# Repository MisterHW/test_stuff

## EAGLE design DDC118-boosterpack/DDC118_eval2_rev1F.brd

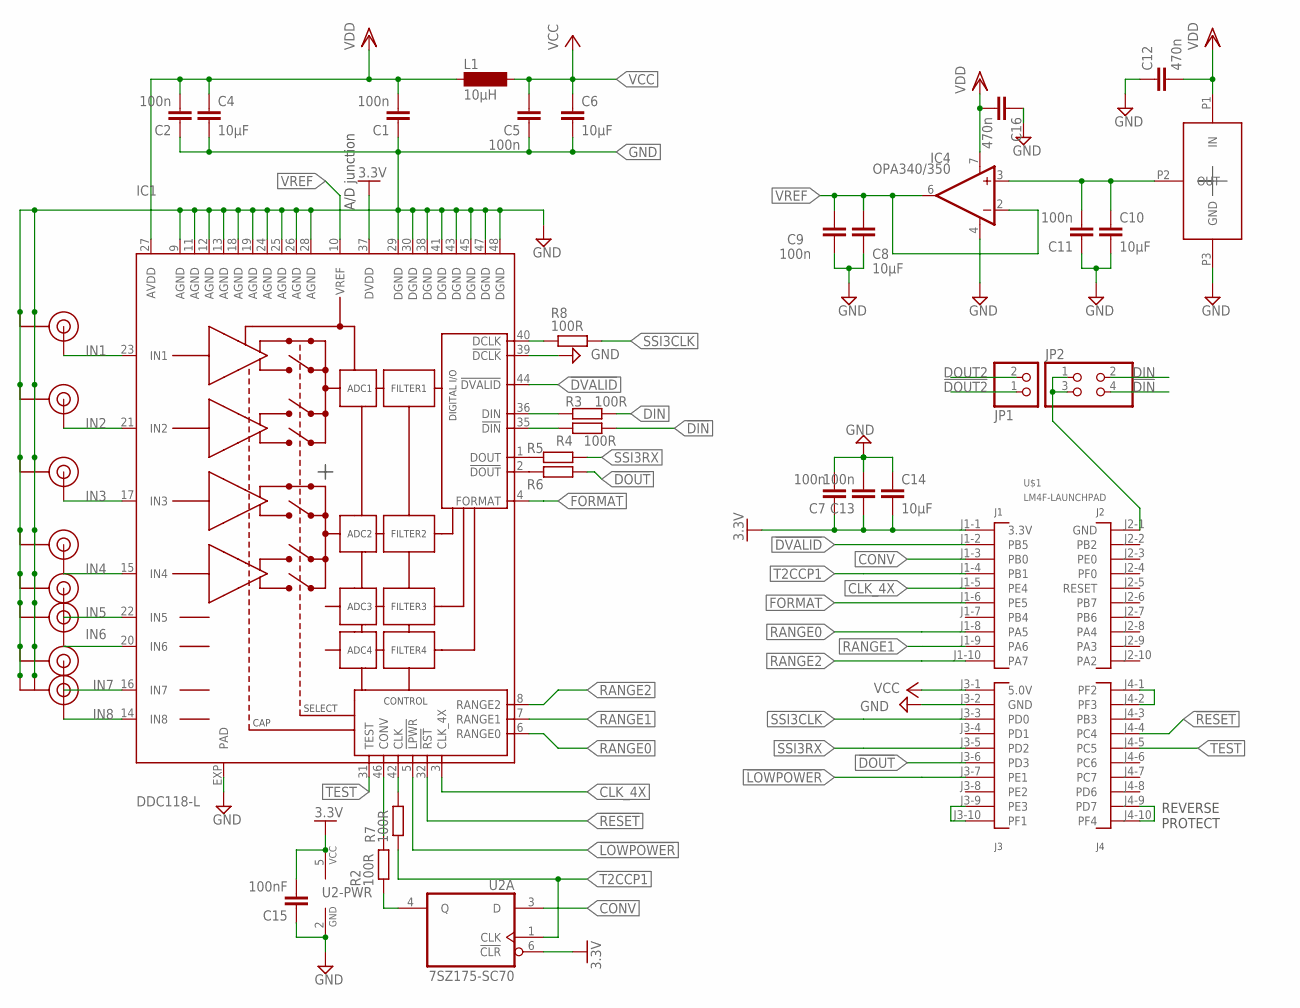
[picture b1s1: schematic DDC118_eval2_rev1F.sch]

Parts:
C1, C2, C5, C7, C9, C11, C13: 100n; C0805K
C4, C6, C8, C10, C14: 10µF; C0805
C12: 470n; C0805K
C15: 100nF; C0603K
C16: 470n; 0805
IC1: DDC118-L; VQFN48-L
IC4: OPA340/350; SO08
JP1: PINHD-1X2_2.54-SMD; 1X02SMD
JP2: PINHD-2X2_2.54-SMD; 2X02SMD
L1: 10µH; MS50
R2, R3, R4, R5, R6, R7, R8: 100R; R0402
U1: REF30XX; SOT-23
U2: 7SZ175-SC70; SC-70
U$1: LM4F-LAUNCHPAD; LM4F120-LAUNCHPAD
U$4, U$5, U$6, U$7, U$8, U$9, U$10, U$11: U.FL

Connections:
!DIN: JP2.4, R4.1
!DOUT: R6.1, U$1.J3-6 (PD3)
!DOUT2: JP1.1
!DVALID: IC1.44 (!DVALID), U$1.J1-2 (PB5)
!LOWPOWER: IC1.5 (!LPWR), U$1.J3-7 (PE1)
!RESET: IC1.32 (!RST), U$1.J4-4 (PC4)
+3.3V: C7.1, C13.1, C14.2, C15.2, IC1.37 (DVDD), U2.5 (VCC), U2.6 (!CLR), U$1.J1-1 (3.3V)
CLK_4X: IC1.3 (CLK_4X), U$1.J1-5 (PE4)
CONV: U2.3 (D), U$1.J1-3 (PB0)
CONV_LATCHED: IC1.46 (CONV), R2.2
DIN: JP2.2, R3.1
DOUT2: JP1.2
FORMAT: IC1.4 (FORMAT), U$1.J1-6 (PE5)
GND: C1.1, C2.1, C4.2, C5.1, C6.2, C7.2, C8.2, C9.1, C10.2, C11.1, C12.1, C13.2, C14.1, C15.1, C16.1, IC1.9 (AGND), IC1.11 (AGND), IC1.12 (AGND), IC1.13 (AGND), IC1.18 (AGND), IC1.19 (AGND), IC1.24 (AGND), IC1.25 (AGND), IC1.26 (AGND), IC1.28 (AGND), IC1.29 (DGND), IC1.30 (DGND), IC1.38 (DGND), IC1.39 (!DCLK), IC1.41 (DGND), IC1.43 (DGND), IC1.45 (DGND), IC1.47 (DGND), IC1.48 (DGND), IC1.EXP (PAD), IC4.4 (V-), U1.P3 (GND), U2.2 (GND), U$1.J3-2 (GND), U$4.P$1 (GND), U$4.P$2 (GND), U$5.P$1 (GND), U$5.P$2 (GND), U$6.P$1 (GND), U$6.P$2 (GND), U$7.P$1 (GND), U$7.P$2 (GND), U$8.P$1 (GND), U$8.P$2 (GND), U$9.P$1 (GND), U$9.P$2 (GND), U$10.P$1 (GND), U$10.P$2 (GND), U$11.P$1 (GND), U$11.P$2 (GND)
IN1: IC1.23 (IN1), U$5.P$3 (SIGNAL)
IN2: IC1.21 (IN2), U$6.P$3 (SIGNAL)
IN3: IC1.17 (IN3), U$7.P$3 (SIGNAL)
IN4: IC1.15 (IN4), U$8.P$3 (SIGNAL)
IN5: IC1.22 (IN5), U$9.P$3 (SIGNAL)
IN6: IC1.20 (IN6), U$4.P$3 (SIGNAL)
IN7: IC1.16 (IN7), U$11.P$3 (SIGNAL)
IN8: IC1.14 (IN8), U$10.P$3 (SIGNAL)
unnamed: R2.1, U2.4 (Q)
unnamed: JP2.1, JP2.3, U$1.J2-1 (GND)
unnamed: IC1.36 (DIN), R3.2
unnamed: IC1.35 (!DIN), R4.2
unnamed: IC1.1 (DOUT), R5.2
unnamed: IC1.2 (!DOUT), R6.2
unnamed: U$1.J4-9 (PD7), U$1.J4-10 (PF4)
unnamed: U$1.J3-9 (PE3), U$1.J3-10 (PF1)
unnamed: U$1.J4-1 (PF2), U$1.J4-2 (PF3)
unnamed: IC1.40 (DCLK), R8.1
unnamed: IC1.42 (CLK), R7.2
unnamed: C10.1, C11.2, IC4.3 (+IN), U1.P2 (OUT)
RANGE0: IC1.6 (RANGE0), U$1.J1-8 (PA5)
RANGE1: IC1.7 (RANGE1), U$1.J1-9 (PA6)
RANGE2: IC1.8 (RANGE2), U$1.J1-10 (PA7)
SSI3CLK: R8.2, U$1.J3-3 (PD0)
SSI3RX: R5.1, U$1.J3-5 (PD2)
T2CCP1: R7.1, U2.1 (CLK), U$1.J1-4 (PB1)
TEST: IC1.31 (TEST), U$1.J4-5 (PC5)
VCC: C5.2, C6.1, L1.2, U$1.J3-1 (5.0V)
VDD: C1.2, C2.2, C4.1, C12.2, C16.2, IC1.27 (AVDD), IC4.7 (V+), L1.1, U1.P1 (IN)
VREF: C8.1, C9.2, IC1.10 (VREF), IC4.2 (-IN), IC4.6 (OUT)

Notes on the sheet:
A/D junction
REVERSE PROTECT

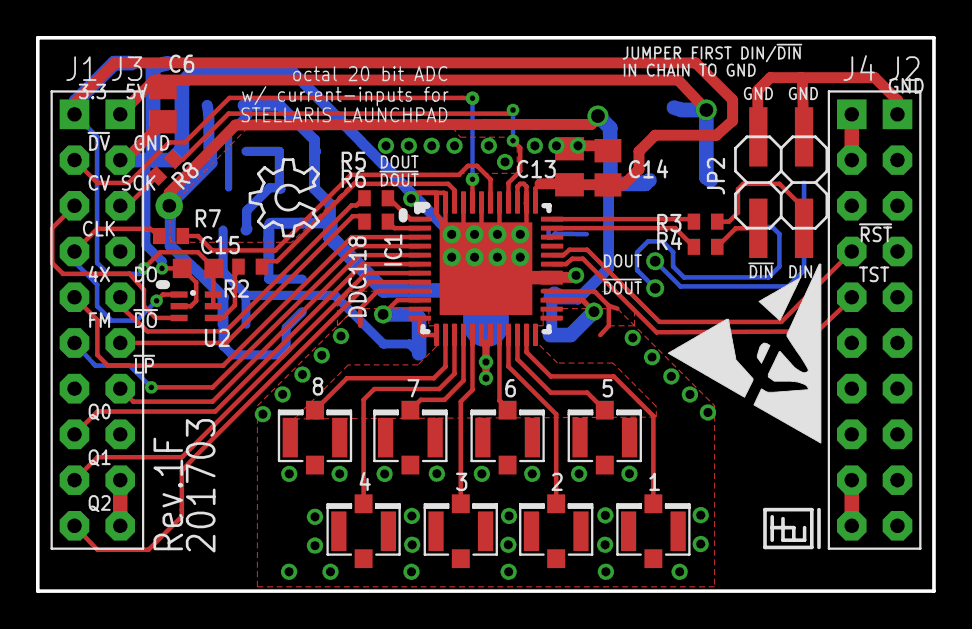
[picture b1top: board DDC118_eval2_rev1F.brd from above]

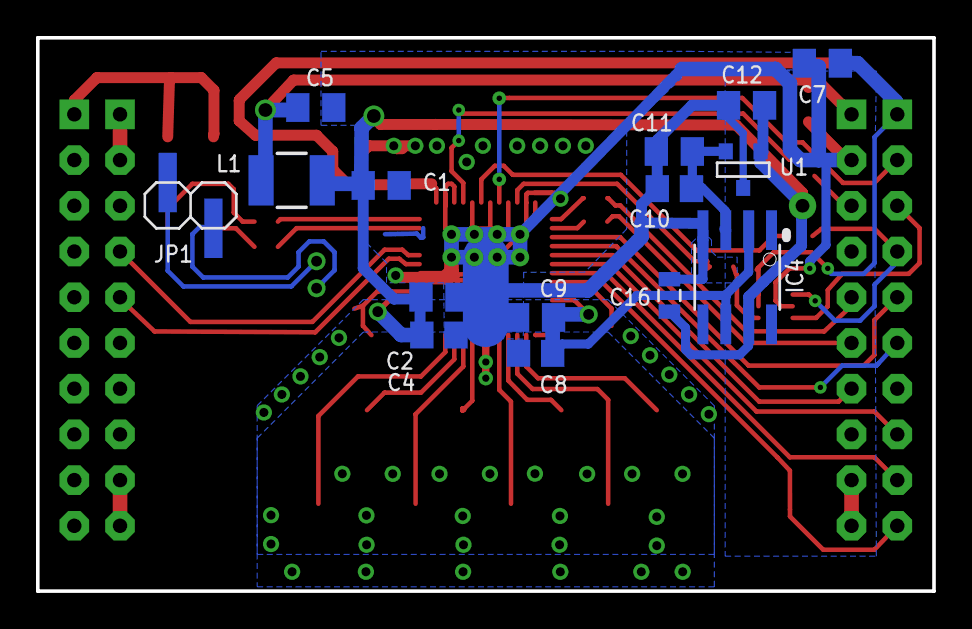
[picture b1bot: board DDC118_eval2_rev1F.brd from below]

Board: 2 copper layers, 49.8 x 30.7 mm, 40 parts (15 on the bottom side), 42 nets.

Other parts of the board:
U$2: OSHW_6X150_NOTEXT
U$3: ESD_10.00

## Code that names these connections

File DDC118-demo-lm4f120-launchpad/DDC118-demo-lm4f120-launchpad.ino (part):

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// pin assignment according to http://energia.nu/img/StellarPadLM4F120H5QR-V1.0.jpg overview graphic and DDC118 booster pack schematic
//

#define DVALIDN PB_5 // PB5
#define CONV PB_0 // PB0, hard coded below
#define T2CCP1 PB_1 // PB1, hard coded below
#define CLK_4X PE_4 // PE4
#define FORMAT PE_5 // PE5
#define RANGE0 PA_5 // PA5
#define RANGE1 PA_6 // PA6
#define RANGE2 PA_7 // PA7
#define SSI3CLK PD_0 // PD0
#define SSI3RX PD_2 // PD2
#define SSI3MOSI PD_3 // PD3 (NC)
#define SSI3CSN PD_1 // PD1 (NC)
#define LOWPWRN PE_1 // PE1
#define RESETN PC_4 // PC4
#define TEST PC_5 // PC5


// GPIO and configuration definitions
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#define CONV_SIDE_B LOW

#define TEST_INACTIVE LOW // under normal operation, inputs are connected. Under TEST mode, inputs are disconnected.
#define TEST_ACTIVE HIGH // starts with next CONV transition. each \_/ toggle during integration adds approx. 11pC
const uint16_t MAX_TEST_Q[8] = {1, 4, 8, 12, 16, 20, 24, 28 }; // MAX_TEST_Q[ANALOG_RANGE_SELECT] appropriate maximum number of 11pC test charge quanta

#define FORMAT_20BIT HIGH
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  // toggle CONV
  if (GPIOPinRead(GPIO_PORTB_BASE, GPIO_PIN_0))
  {
    GPIOPinWrite(GPIO_PORTB_BASE, GPIO_PIN_0, 0); // next CONV side B
  } else {
    GPIOPinWrite(GPIO_PORTB_BASE, GPIO_PIN_0, GPIO_PIN_0); // next CONV side A
  }

}
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
void setup_DVALIDN_interrupt(void)
{
  //configure PB5 falling edge interrupt, attach PORTBPinIntHandler()
  GPIOIntRegister(GPIO_PORTB_BASE, PORTBPinIntHandler);
  GPIOPinTypeGPIOInput(GPIO_PORTB_BASE, GPIO_PIN_5);
  GPIOIntTypeSet(GPIO_PORTB_BASE, GPIO_PIN_5, GPIO_FALLING_EDGE);
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void DDC118_init(void)
{
  pinMode(DVALIDN, INPUT);
  pinMode(RANGE0, OUTPUT);  digitalWrite(RANGE0, RANGE_BIT_0(ANALOG_RANGE_SELECT));
  pinMode(RANGE1, OUTPUT);  digitalWrite(RANGE1, RANGE_BIT_1(ANALOG_RANGE_SELECT));
  pinMode(RANGE2, OUTPUT);  digitalWrite(RANGE2, RANGE_BIT_2(ANALOG_RANGE_SELECT));
  pinMode(CLK_4X, OUTPUT);  digitalWrite(CLK_4X, DDC_SYSTEM_CLOCK_PRESCALER);
  pinMode(RESETN, OUTPUT);  digitalWrite(RESETN, LOW); delay(1); digitalWrite(RESETN, HIGH); delay(10);
  pinMode(LOWPWRN, OUTPUT); digitalWrite(LOWPWRN, LOWPWRN_HIGHSPEED);
  setup_T2CCP1_clock_source();
  pinMode(CONV, OUTPUT);    digitalWrite(CONV, CONV_SIDE_A);
  setup_CONV_clock_source();
  pinMode(TEST, OUTPUT);    digitalWrite(TEST, TEST_INACTIVE);
  setup_DVALIDN_interrupt();
  pinMode(FORMAT, OUTPUT);  digitalWrite(FORMAT, FORMAT_20BIT);
}


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
void setup() {
  pinMode(SSI3CSN, OUTPUT);
  pinMode(SSI3CLK, OUTPUT);
  pinMode(SSI3RX, INPUT);
  SPI.setModule(3);
  SPI.begin();
  SPI.setDataMode(SPI_MODE0);
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
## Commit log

2017-01-07 initial commit of code from https://github.com/repaper/gratis for reference
2017-01-07 initial commit (code tested w/ hardware)
2017-01-07 renaming...
2017-01-07 renaming done
2017-01-07 - FLASH : rejected as additional library possibly due to name collision, fix: rename specialized external SPI flash driver to EPD_Flash (has hard coded stuff that is not generalized) - S5813A : add L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
2017-01-07 slower demo settings with more obvious 115200 8N1
2017-01-08 - implements baseline and side A-B bias compensation by baseline acquisition and side-specific subtraction - prepares for charge injection test mode (will have to happen in the timer ISR soon after C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
2017-01-14 EPD.cpp: right now there doesn't seem to be LM4F120 analogFrequency() support, EPD_PWM pin is no GPTM selectable PWM output TnCCPm so the "just make it work" approach is to run the charge pump for a 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
2017-03-27 commit all revisions of the DDC118 launchpad boosterpack PCB (2014-2017)
2017-03-27 minor optimizations

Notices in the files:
parts and their libraries:
SparkFun-Capacitors: Licensing: CC v3.0 Share-Alike You are welcome to use this library for commercial purposes.
m-pad-2.1: License : GNU General Public License version 2 (see bottom)
